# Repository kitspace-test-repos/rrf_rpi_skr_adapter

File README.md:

Raspberry Pi to SKR/SKR Pro Adapter for ReprapFirmware
======================================================

The adapter sold by TeamGloomy on Tindie for this purpose is sold out.  This
is my equivalent replacement.

Description
-----------

I'm looking at putting ReprapFirmware on my Hypercube 300.  The necessary
adapter to connect its Raspberry Pi Zero 2 W to its SKR Pro 1.2 is
out-of-stock on Tindie.  This is a smaller adapter that does the same thing,
only it plugs into the EXP2 header on the printer motherboard and a 6-wire
cable connects the other end to pins 19-24 on the Raspberry Pi GPIO header. 
(I already have a 4-wire UART connection between the two that also supplies
power; instead of putting in the full 40-pin GPIO header, it only has enough
pins populated for the connections I'm using.)

It was a quick layout to throw together in KiCad; I probably spent more time
playing around with panelization options than on the main layout.  :) I
should have 100 (20x5) bare boards arriving from JLCPCB, and the parts to go
on it are dirt-cheap…should be well under $5 from DigiKey, and probably
under $1 each in quantity from LCSC.

This project is also on
[printables.com](https://www.printables.com/model/262089-raspberry-pi-to-skrskr-pro-adapter-for-reprapfirmw).

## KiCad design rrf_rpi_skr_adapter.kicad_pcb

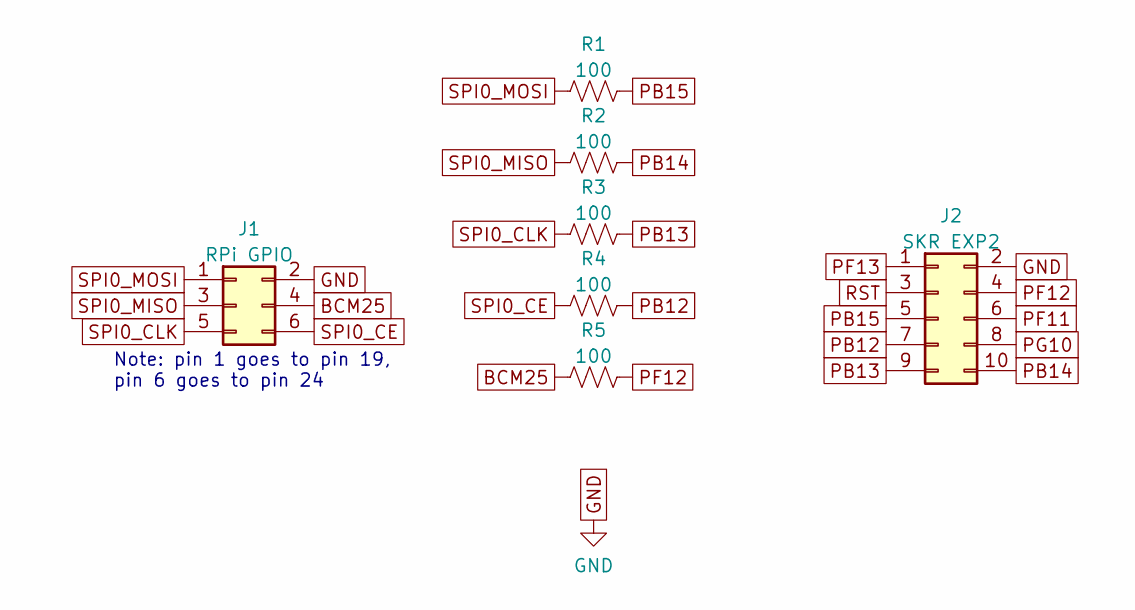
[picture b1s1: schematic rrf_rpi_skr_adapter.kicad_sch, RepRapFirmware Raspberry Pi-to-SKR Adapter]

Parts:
J1: RPi GPIO; PinHeader_2x03_P2.54mm_Horizontal; MPN PH2RA-06-UA; DigiKey_SKU 2057-PH2RA-06-UA-ND
J2: SKR EXP2; PinSocket_2x05_P2.54mm_Horizontal; MPN SFH11-PBPC-D05-RA-BK; DigiKey_SKU S9202-ND
R1, R2, R3, R4, R5: 100; R_0603_1608Metric; MPN RC0603FR-07100RL; DigiKey_SKU 311-100HRCT-ND

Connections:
BCM25: J1.4, R5.1
GND: J1.2, J2.2
PB12: J2.7, R4.2
PB13: J2.9, R3.2
PB14: J2.10, R2.2
PB15: J2.5, R1.2
PF11: J2.6
PF12: J2.4, R5.2
PF13: J2.1
PG10: J2.8
RST: J2.3
SPI0_CE: J1.6, R4.1
SPI0_CLK: J1.5, R3.1
SPI0_MISO: J1.3, R2.1
SPI0_MOSI: J1.1, R1.1

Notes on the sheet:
Note: pin 1 goes to pin 19, pin 6 goes to pin 24

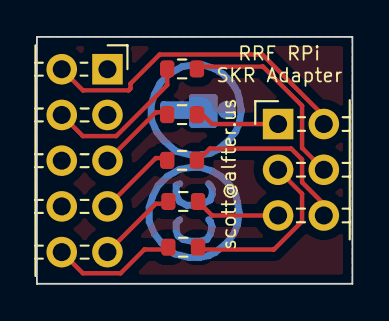
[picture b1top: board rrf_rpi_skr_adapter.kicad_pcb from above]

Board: 2 copper layers, 17.5 x 13.7 mm, 7 parts (0 on the bottom side), 11 nets.

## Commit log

2022-08-19 missing newline at end of file
2022-08-20 add rendering
2022-10-28 add docs
2022-10-28 add kitspace.yaml
2022-12-01 separate panelized gerbers into their own directory for Kitspace
2022-12-02 Fix kitspace.yaml, add panel
